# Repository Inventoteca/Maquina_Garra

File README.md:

# Maquina_Garra
Repo para documentar el proyecto del sistema de seguridad para la máquina de la garra, ante inclinaciones se bloquee y sólo al recibir un pulso entonces se abra.

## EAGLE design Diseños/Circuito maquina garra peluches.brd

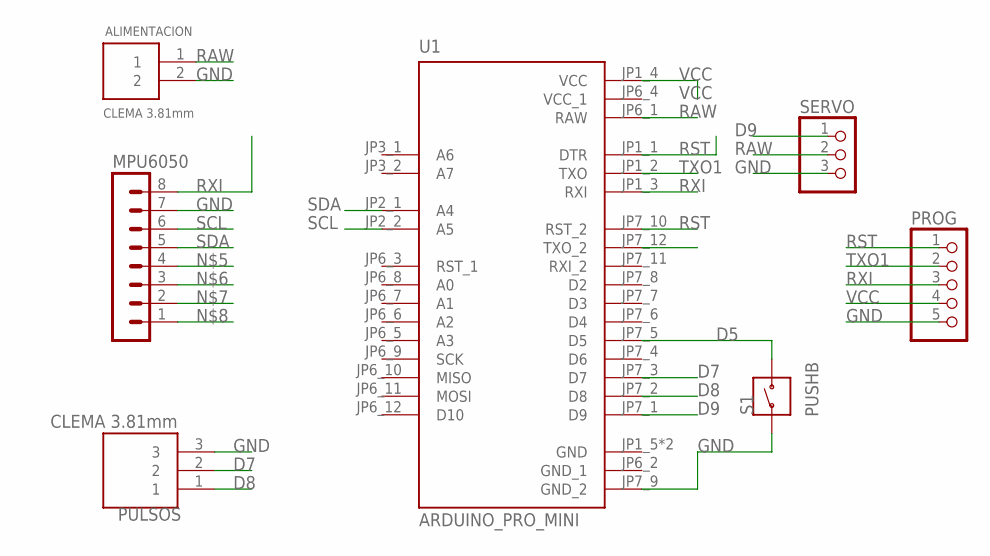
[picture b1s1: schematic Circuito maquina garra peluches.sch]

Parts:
ALIMENTACION: CLEMA 3.81mm; TE_1776113-2
MPU6050: MA08-1
PROG: PINHD-1X5; 1X05
PULSOS: CLEMA 3.81mm; TE_284392-3
S1: PUSHB; SW_4-1437565-0
SERVO: PINHD-1X3/90; 1X03/90
U1: ARDUINO_PRO_MINI; MODULE_ARDUINO_PRO_MINI

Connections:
D5: S1.2, U1.JP7_5 (D5)
D7: PULSOS.2, U1.JP7_3 (D7)
D8: PULSOS.1, U1.JP7_2 (D8)
D9: SERVO.1, U1.JP7_1 (D9)
GND: ALIMENTACION.2, MPU6050.7, PROG.5, PULSOS.3, S1.1, SERVO.3, U1.JP1_5 (GND), U1.JP1_6 (GND), U1.JP7_9 (GND_2)
GND_1: U1.JP6_2 (GND_1)
RAW: ALIMENTACION.1, SERVO.2, U1.JP6_1 (RAW)
RST: PROG.1, U1.JP1_1 (DTR), U1.JP7_10 (RST_2)
RXI: MPU6050.8, PROG.3, U1.JP1_3 (RXI)
SCL: MPU6050.6, U1.JP2_2 (A5)
SDA: MPU6050.5, U1.JP2_1 (A4)
TXO1: PROG.2, U1.JP1_2 (TXO)
VCC: PROG.4, U1.JP1_4 (VCC)
VCC_1: U1.JP6_4 (VCC_1)

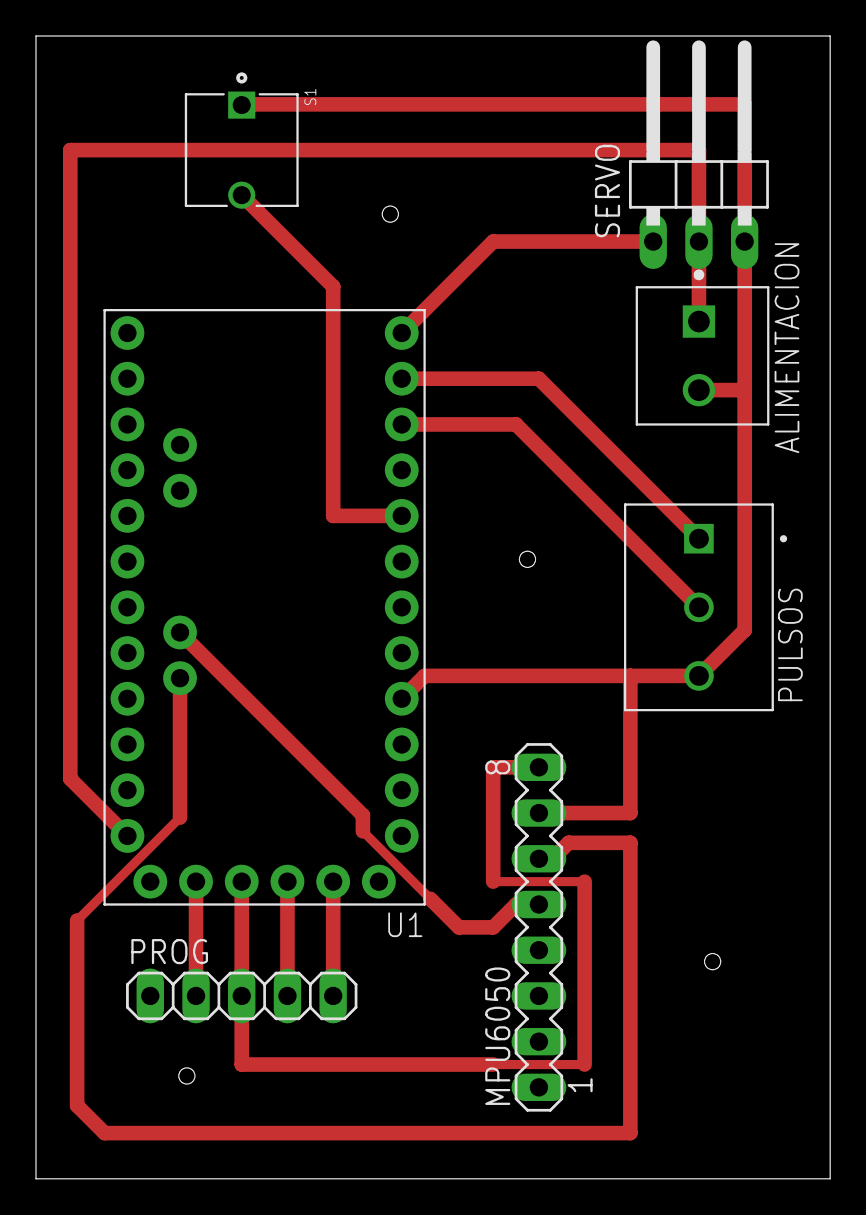
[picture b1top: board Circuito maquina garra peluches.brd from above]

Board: 2 copper layers, 44.1 x 63.5 mm, 7 parts (0 on the bottom side), 12 nets.

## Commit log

2021-10-13 cambio a LSM9DS1
    Se cambió a LSM9DS1 temporalmente para conseguir otro MPU
2021-10-16 MPU
    se regresó a MPU y añadió una función de calibración pero no funcionó
2021-10-18 Limpieza de código
2021-10-19 Servo y pulsos
    Se envía el documento correcto con las funciones designadas a controlar el servo y los pulsos de comunicación
2021-10-19 Implementación de función de calibración
    primer intento de implementar una función de calibración
2021-10-20 calzador servo
2021-10-20 Función de calibración
    Se implementó la función de calibración en el código y se ajustaron valores de taolerancias
2021-10-20 Código casi funcional
    problemas con los detach
2021-10-20 Diseño PCB en Eagle y esquemático
2021-10-21 comentar el detach
2021-10-21 código comentado
    Se comentó el código para que se entienda mejor
2021-10-21 cambios revisión Carlos
2021-10-21 Codigo refactorizado
2021-10-21 Código con guardado de calibración en EEPROM
2021-10-22 cambios menores
2021-10-22 versión 2 circuito
2021-10-22 version2 circuito
2021-10-22 corrección circuito v2
2021-10-24 avances documentación
2021-10-24 código completo
    Código cargado en la placa entregada al cliente
